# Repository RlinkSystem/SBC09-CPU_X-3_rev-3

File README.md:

# SBC09-CPU_X-3_rev-3

Simple SBC design around MC6809 Revision 3

This is the second atemp/test to make a full SBC system based on my old
modem X-3 construction, and keep it simpel.

This was done during Summer holiday 2025.
To test my simple & basic setup, and continue to experiment.

My goal is to have an uncomplex build that is not compact, so:
* not with a few large ICs
* not with PAL/GAL
* and with "many" ICs

So my setup is:
* CPU: MC68B09/HD63C09
* MEM: 7x HM6264ALP-15
* ROM: 2764 eq EPROM / EEPROM
* PTM: MC6840
* ACIA: 2x MC6850
* ACIA: R6551
* PIA: 3x MC6821
* Glue logic:
  * 74HCT04
  * 4x 74HCT138
  * 74HCT4040 Baud Rate
* Test support for USB-TTL-UART
  * CH340E (CH340X)

My testing setup:

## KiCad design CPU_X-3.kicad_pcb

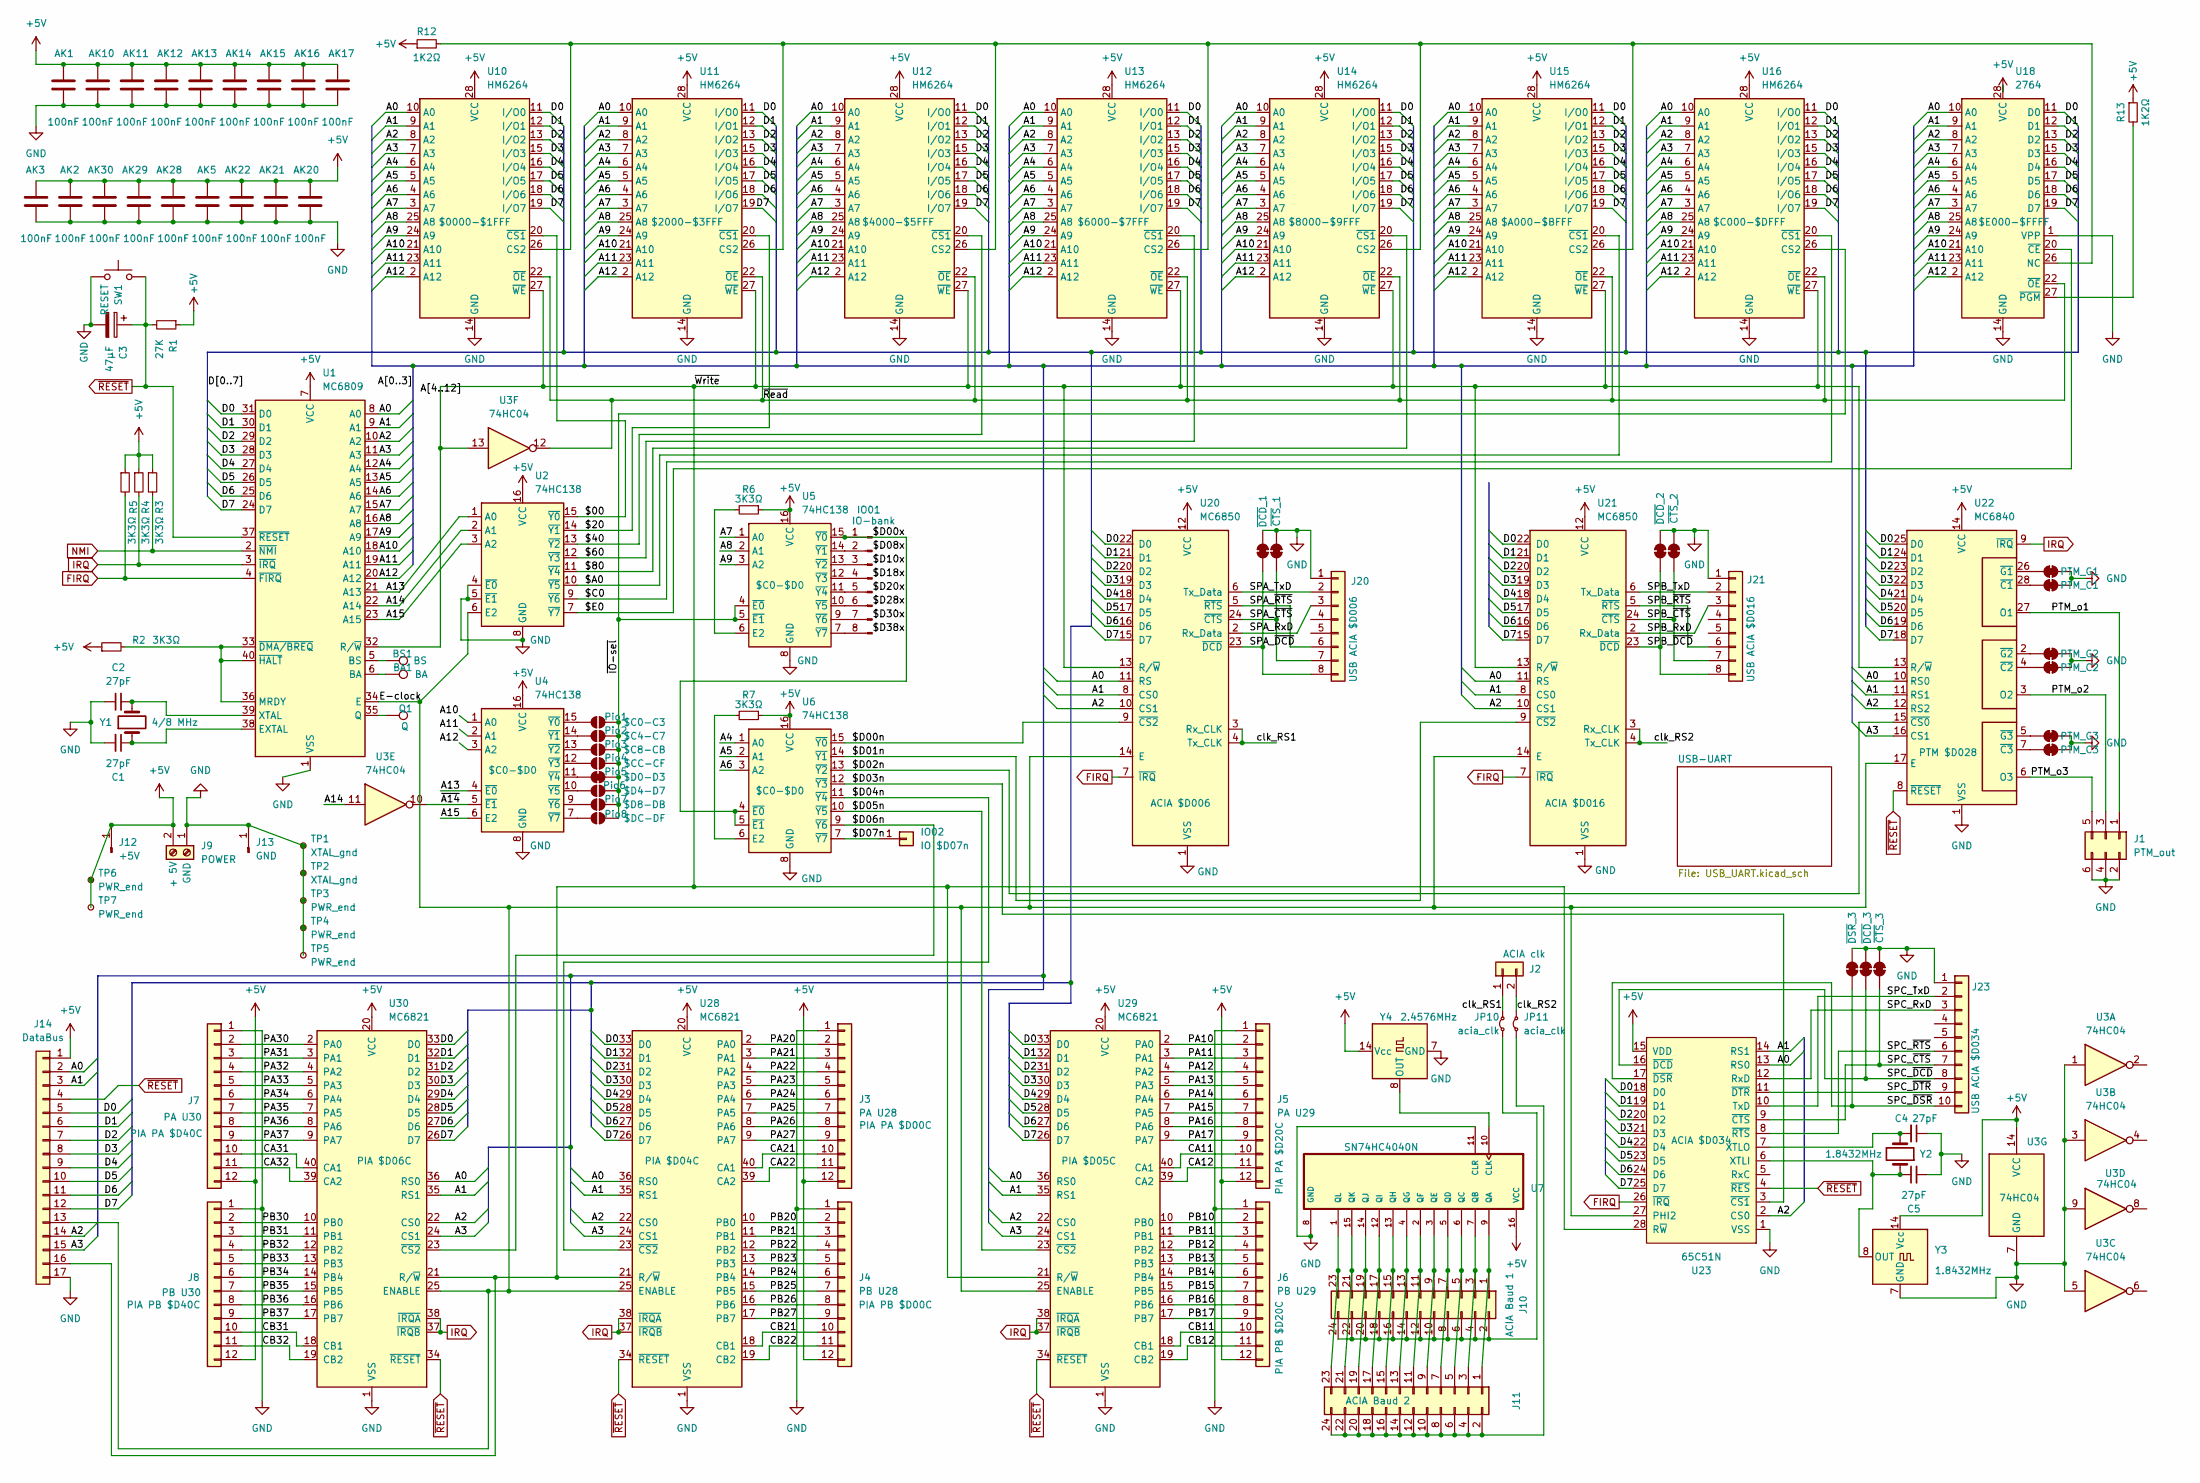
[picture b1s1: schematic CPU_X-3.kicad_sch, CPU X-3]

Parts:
AK1, AK2, AK3, AK5, AK28, AK29, AK30: 100nF; Avkopplings_C
AK10, AK11, AK12, AK13, AK14, AK15, AK16, AK17, AK20, AK21, AK22: 100nF; Avkoppling_LC
BA1: BA; TestPoint_Pad_1.5x1.5mm
BS1: BS; TestPoint_Pad_1.5x1.5mm
C1, C2, C4, C5: 27pF; C_Rect_L4.0mm_W2.5mm_P2.50mm
C3: 47µF; CP_Axial_L11.0mm_D6.0mm_P18.00mm_Horizontal
IO01: IO-bank; PinSocket_1x08_P2.54mm_Vertical
IO02: IO $D07n; PinSocket_1x01_P2.54mm_Vertical
J1: PTM_out; PinHeader_2x03_P2.54mm_Vertical
J2: ACIA clk; PinHeader_1x02_P2.54mm_Vertical
J3: PA U28; PinHeader_1x12_P2.54mm_Vertical
J4: PB U28; PinHeader_1x12_P2.54mm_Vertical
J5: PA U29; PinHeader_1x12_P2.54mm_Vertical
J6: PB U29; PinHeader_1x12_P2.54mm_Vertical
J7: PA U30; PinHeader_1x12_P2.54mm_Vertical
J8: PB U30; PinHeader_1x12_P2.54mm_Vertical
J9: POWER; TerminalBlock_MetzConnect_Type101_RT01602HBWC_1x02_P5.08mm_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
J10: ACIA Baud 1; PinHeader_2x12_P2.54mm_Vertical
J11: ACIA Baud 2; PinHeader_2x12_P2.54mm_Vertical
J12: +5V; Pin_D1.0mm_L10.0mm_LooseFit
J13: GND; Pin_D1.0mm_L10.0mm_LooseFit
J14: DataBus; PinHeader_1x17_P2.54mm_Vertical
J20: USB ACIA $D006; PinSocket_1x08_P2.54mm_Vertical
J21: USB ACIA $D016; PinSocket_1x08_P2.54mm_Vertical
J23: USB ACIA $D034; PinSocket_1x10_P2.54mm_Vertical
JP10, JP11: acia_clk; SolderJumper-2_P1.3mm_Bridged_RoundedPad1.0x1.5mm
PTM_C1, PTM_C2, PTM_C3: PTM_1; SolderJumper-2_P1.3mm_Bridged_Pad1.0x1.5mm
PTM_G1, PTM_G2, PTM_G3: PTM_1; SolderJumper-2_P1.3mm_Bridged_Pad1.0x1.5mm
Pio1: $C0-C3; SolderJumper-2_P1.3mm_Open_RoundedPad1.0x1.5mm
Pio2: $C4-C7; SolderJumper-2_P1.3mm_Open_RoundedPad1.0x1.5mm
Pio3: $C8-CB; SolderJumper-2_P1.3mm_Open_RoundedPad1.0x1.5mm
Pio4: $CC-CF; SolderJumper-2_P1.3mm_Open_RoundedPad1.0x1.5mm
Pio5: $D0-D3; SolderJumper-2_P1.3mm_Bridged_RoundedPad1.0x1.5mm
Pio6: $D4-D7; SolderJumper-2_P1.3mm_Open_RoundedPad1.0x1.5mm
Pio7: $D8-DB; SolderJumper-2_P1.3mm_Open_RoundedPad1.0x1.5mm
Pio8: $DC-DF; SolderJumper-2_P1.3mm_Open_RoundedPad1.0x1.5mm
Q1: Q; TestPoint_Pad_1.5x1.5mm
R1: 27K; R_Axial_DIN0207_L6.3mm_D2.5mm_P10.16mm_Horizontal
R2, R3, R4, R5, R6, R7: 3K3Ω; R_Axial_DIN0207_L6.3mm_D2.5mm_P10.16mm_Horizontal
R12: 1K2Ω; R_Axial_PullUp_long
R13: 1K2Ω; R_Axial_DIN0207_L6.3mm_D2.5mm_P10.16mm_Horizontal
SW1: RESET; SW_PUSH_1P1T_6x3.5mm_H5.0_APEM_MJTP1250
TP1, TP2: XTAL_gnd; TestPoint_Pad_D1.0mm
TP3, TP4, TP5, TP6, TP7: PWR_end; TestPoint_Pad_D1.0mm
U1: MC6809; DIP-40_W15.24mm_Socket_LongPads
U2, U4, U5, U6: 74HC138; DIP-16_W7.62mm_Socket_LongPads
U3: 74HC04; DIP-14_W7.62mm_Socket_LongPads
U7: SN74HC4040N; DIP-16_W7.62mm_Socket_LongPads
U10, U11, U12, U13, U14, U16: HM6264; X3-MEM_DIP-28
U15: HM6264; DIP_Socket-28_W11.9_W12.7_W15.24_W17.78_W18.5_3M_228-1277-0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
U18: 2764; X3-MEM_DIP-28
U20, U21: MC6850; DIP-24_18.0mmx34.29mm_W15.24mm_Socket_LongPads
U22: MC6840; DIP-28_W15.24mm_Socket_LongPads
U23: 65C51N; DIP-28_W15.24mm
U28, U29, U30: MC6821; X3-IO_DIP-40
Y1: 4/8 MHz; Resonator-2Pin_W10.0mm_H5.0mm
Y2: 1.8432MHz; Resonator-2Pin_W10.0mm_H5.0mm
Y3: 1.8432MHz; Oscillator_DIP-14
Y4: 2.4576MHz; Oscillator_DIP-14
~{CTS}_1: UART-A; SolderJumper-2_P1.3mm_Bridged_Pad1.0x1.5mm
~{CTS}_2: UART-B; SolderJumper-2_P1.3mm_Bridged_Pad1.0x1.5mm
~{CTS}_3: UART-C; SolderJumper-2_P1.3mm_Bridged_Pad1.0x1.5mm
~{DCD}_1: UART-A; SolderJumper-2_P1.3mm_Bridged_Pad1.0x1.5mm
~{DCD}_2: UART-B; SolderJumper-2_P1.3mm_Bridged_Pad1.0x1.5mm
~{DCD}_3: UART-C; SolderJumper-2_P1.3mm_Bridged_Pad1.0x1.5mm
~{DSR}_3: UART-C; SolderJumper-2_P1.3mm_Bridged_Pad1.0x1.5mm

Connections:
+5V: AK1.1, AK2.1, AK3.1, AK5.1, AK10.1, AK11.1, AK12.1, AK13.1, AK14.1, AK15.1, AK16.1, AK17.1, AK20.1, AK21.1, AK22.1, AK28.1, AK29.1, AK30.1, J3.12, J4.12, J5.12, J6.12, J7.12, J8.12, J9.2, J12.1, J14.1, R1.1, R2.1, R3.1, R4.1, R5.1, R6.1, R7.1, R12.1, R13.1, TP6.1, TP7.1, U1.7 (VCC), U2.16 (VCC), U3.14 (VCC), U4.16 (VCC), U5.16 (VCC), U6.16 (VCC), U7.16 (VCC), U10.28 (VCC), U11.28 (VCC), U12.28 (VCC), U13.28 (VCC), U14.28 (VCC), U15.28 (VCC), U16.28 (VCC), U18.28 (VCC), U20.12 (VCC), U21.12 (VCC), U22.14 (VCC), U23.15 (VDD), U28.20 (VCC), U29.20 (VCC), U30.20 (VCC), Y3.14 (Vcc), Y4.14 (Vcc); also elsewhere on the board
/$00: U2.15 (~Y0), U10.20 (~CS1)
/$20: U2.14 (~Y1), U11.20 (~CS1)
/$40: U2.13 (~Y2), U12.20 (~CS1)
/$60: U2.12 (~Y3), U13.20 (~CS1)
/$80: U2.11 (~Y4), U14.20 (~CS1)
/$A0: U2.10 (~Y5), U15.20 (~CS1)
/$C0: U2.9 (~Y6), U16.20 (~CS1)
/$D00n: U6.15 (~Y0), U20.9 (~CS2)
/$D00x: IO01.1, U5.15 (~Y0), U6.4 (~E0), U6.5 (~E1)
/$D01n: U6.14 (~Y1), U21.9 (~CS2)
/$D02n: U6.13 (~Y2), U22.15 (~CS0)
/$D03n: U6.12 (~Y3), U23.3 (~CS1)
/$D04n: U6.11 (~Y4), U28.23 (~CS2)
/$D05n: U6.10 (~Y5), U29.23 (~CS2)
/$D06n: U6.9 (~Y6), U30.23 (~CS2)
/$D07n: IO02.1, U6.7 (~Y7)
/$E0: U2.7 (~Y7), U18.20 (~CE)
/A0: J14.2, U1.8 (A0), U10.10 (A0), U11.10 (A0), U12.10 (A0), U13.10 (A0), U14.10 (A0), U15.10 (A0), U16.10 (A0), U18.10 (A0), U20.11 (RS), U21.11 (RS), U22.10 (RS0), U23.13 (RS0), U28.36 (RS0), U29.36 (RS0), U30.36 (RS0)
/A1: J14.3, U1.9 (A1), U10.9 (A1), U11.9 (A1), U12.9 (A1), U13.9 (A1), U14.9 (A1), U15.9 (A1), U16.9 (A1), U18.9 (A1), U20.8 (CS0), U21.8 (CS0), U22.11 (RS1), U23.14 (RS1), U28.35 (RS1), U29.35 (RS1), U30.35 (RS1)
/A2: J14.14, U1.10 (A2), U10.8 (A2), U11.8 (A2), U12.8 (A2), U13.8 (A2), U14.8 (A2), U15.8 (A2), U16.8 (A2), U18.8 (A2), U20.10 (CS1), U21.10 (CS1), U22.12 (RS2), U23.2 (CS0), U28.22 (CS0), U29.22 (CS0), U30.22 (CS0)
/A3: J14.15, U1.11 (A3), U10.7 (A3), U11.7 (A3), U12.7 (A3), U13.7 (A3), U14.7 (A3), U15.7 (A3), U16.7 (A3), U18.7 (A3), U22.16 (CS1), U28.24 (CS1), U29.24 (CS1), U30.24 (CS1)
/A4: U1.12 (A4), U6.1 (A0), U10.6 (A4), U11.6 (A4), U12.6 (A4), U13.6 (A4), U14.6 (A4), U15.6 (A4), U16.6 (A4), U18.6 (A4)
/A5: U1.13 (A5), U6.2 (A1), U10.5 (A5), U11.5 (A5), U12.5 (A5), U13.5 (A5), U14.5 (A5), U15.5 (A5), U16.5 (A5), U18.5 (A5)
/A6: U1.14 (A6), U6.3 (A2), U10.4 (A6), U11.4 (A6), U12.4 (A6), U13.4 (A6), U14.4 (A6), U15.4 (A6), U16.4 (A6), U18.4 (A6)
/A7: U1.15 (A7), U5.1 (A0), U10.3 (A7), U11.3 (A7), U12.3 (A7), U13.3 (A7), U14.3 (A7), U15.3 (A7), U16.3 (A7), U18.3 (A7)
/A8: U1.16 (A8), U5.2 (A1), U10.25 (A8), U11.25 (A8), U12.25 (A8), U13.25 (A8), U14.25 (A8), U15.25 (A8), U16.25 (A8), U18.25 (A8)
/A9: U1.17 (A9), U5.3 (A2), U10.24 (A9), U11.24 (A9), U12.24 (A9), U13.24 (A9), U14.24 (A9), U15.24 (A9), U16.24 (A9), U18.24 (A9)
/A10: U1.18 (A10), U4.1 (A0), U10.21 (A10), U11.21 (A10), U12.21 (A10), U13.21 (A10), U14.21 (A10), U15.21 (A10), U16.21 (A10), U18.21 (A10)
/A11: U1.19 (A11), U4.2 (A1), U10.23 (A11), U11.23 (A11), U12.23 (A11), U13.23 (A11), U14.23 (A11), U15.23 (A11), U16.23 (A11), U18.23 (A11)
/A12: U1.20 (A12), U4.3 (A2), U10.2 (A12), U11.2 (A12), U12.2 (A12), U13.2 (A12), U14.2 (A12), U15.2 (A12), U16.2 (A12), U18.2 (A12)
/A13: U1.21 (A13), U2.1 (A0), U4.4 (~E0)
/A14: U1.22 (A14), U2.2 (A1), U3.11
/A15: U1.23 (A15), U2.3 (A2), U4.6 (E2)
/CA11: J5.10, U29.40 (CA1)
/CA12: J5.11, U29.39 (CA2)
/CA21: J3.10, U28.40 (CA1)
/CA22: J3.11, U28.39 (CA2)
/CA31: J7.10, U30.40 (CA1)
/CA32: J7.11, U30.39 (CA2)
/CB11: J6.10, U29.18 (CB1)
/CB12: J6.11, U29.19 (CB2)
/CB21: J4.10, U28.18 (CB1)
/CB22: J4.11, U28.19 (CB2)
/CB31: J8.10, U30.18 (CB1)
/CB32: J8.11, U30.19 (CB2)
/D0: J14.5, U1.31 (D0), U10.11 (I/O0), U11.11 (I/O0), U12.11 (I/O0), U13.11 (I/O0), U14.11 (I/O0), U15.11 (I/O0), U16.11 (I/O0), U18.11 (D0), U20.22 (D0), U21.22 (D0), U22.25 (D0), U23.18 (D0), U28.33 (D0), U29.33 (D0), U30.33 (D0)
/D1: J14.6, U1.30 (D1), U10.12 (I/O1), U11.12 (I/O1), U12.12 (I/O1), U13.12 (I/O1), U14.12 (I/O1), U15.12 (I/O1), U16.12 (I/O1), U18.12 (D1), U20.21 (D1), U21.21 (D1), U22.24 (D1), U23.19 (D1), U28.32 (D1), U29.32 (D1), U30.32 (D1)
/D2: J14.7, U1.29 (D2), U10.13 (I/O2), U11.13 (I/O2), U12.13 (I/O2), U13.13 (I/O2), U14.13 (I/O2), U15.13 (I/O2), U16.13 (I/O2), U18.13 (D2), U20.20 (D2), U21.20 (D2), U22.23 (D2), U23.20 (D2), U28.31 (D2), U29.31 (D2), U30.31 (D2)
/D3: J14.8, U1.28 (D3), U10.15 (I/O3), U11.15 (I/O3), U12.15 (I/O3), U13.15 (I/O3), U14.15 (I/O3), U15.15 (I/O3), U16.15 (I/O3), U18.15 (D3), U20.19 (D3), U21.19 (D3), U22.22 (D3), U23.21 (D3), U28.30 (D3), U29.30 (D3), U30.30 (D3)
/D4: J14.9, U1.27 (D4), U10.16 (I/O4), U11.16 (I/O4), U12.16 (I/O4), U13.16 (I/O4), U14.16 (I/O4), U15.16 (I/O4), U16.16 (I/O4), U18.16 (D4), U20.18 (D4), U21.18 (D4), U22.21 (D4), U23.22 (D4), U28.29 (D4), U29.29 (D4), U30.29 (D4)
/D5: J14.10, U1.26 (D5), U10.17 (I/O5), U11.17 (I/O5), U12.17 (I/O5), U13.17 (I/O5), U14.17 (I/O5), U15.17 (I/O5), U16.17 (I/O5), U18.17 (D5), U20.17 (D5), U21.17 (D5), U22.20 (D5), U23.23 (D5), U28.28 (D5), U29.28 (D5), U30.28 (D5)
/D6: J14.11, U1.25 (D6), U10.18 (I/O6), U11.18 (I/O6), U12.18 (I/O6), U13.18 (I/O6), U14.18 (I/O6), U15.18 (I/O6), U16.18 (I/O6), U18.18 (D6), U20.16 (D6), U21.16 (D6), U22.19 (D6), U23.24 (D6), U28.27 (D6), U29.27 (D6), U30.27 (D6)
/D7: J14.12, U1.24 (D7), U10.19 (I/O7), U11.19 (I/O7), U12.19 (I/O7), U13.19 (I/O7), U14.19 (I/O7), U15.19 (I/O7), U16.19 (I/O7), U18.19 (D7), U20.15 (D7), U21.15 (D7), U22.18 (D7), U23.25 (D7), U28.26 (D7), U29.26 (D7), U30.26 (D7)
/E-clock: J14.13, U1.34 (E), U2.6 (E2), U20.14 (E), U21.14 (E), U22.17 (E), U23.27 (PHI2), U28.25 (ENABLE), U29.25 (ENABLE), U30.25 (ENABLE)
/PA10: J5.2, U29.2 (PA0)
/PA11: J5.3, U29.3 (PA1)
/PA12: J5.4, U29.4 (PA2)
/PA13: J5.5, U29.5 (PA3)
/PA14: J5.6, U29.6 (PA4)
/PA15: J5.7, U29.7 (PA5)
/PA16: J5.8, U29.8 (PA6)
/PA17: J5.9, U29.9 (PA7)
/PA20: J3.2, U28.2 (PA0)
/PA21: J3.3, U28.3 (PA1)
/PA22: J3.4, U28.4 (PA2)
/PA23: J3.5, U28.5 (PA3)
/PA24: J3.6, U28.6 (PA4)
/PA25: J3.7, U28.7 (PA5)
/PA26: J3.8, U28.8 (PA6)
/PA27: J3.9, U28.9 (PA7)
/PA30: J7.2, U30.2 (PA0)
/PA31: J7.3, U30.3 (PA1)
/PA32: J7.4, U30.4 (PA2)
/PA33: J7.5, U30.5 (PA3)
/PA34: J7.6, U30.6 (PA4)
/PA35: J7.7, U30.7 (PA5)
/PA36: J7.8, U30.8 (PA6)
/PA37: J7.9, U30.9 (PA7)
/PB10: J6.2, U29.10 (PB0)
/PB11: J6.3, U29.11 (PB1)
/PB12: J6.4, U29.12 (PB2)
/PB13: J6.5, U29.13 (PB3)
/PB14: J6.6, U29.14 (PB4)
/PB15: J6.7, U29.15 (PB5)
/PB16: J6.8, U29.16 (PB6)
/PB17: J6.9, U29.17 (PB7)
/PB20: J4.2, U28.10 (PB0)
/PB21: J4.3, U28.11 (PB1)
/PB22: J4.4, U28.12 (PB2)
/PB23: J4.5, U28.13 (PB3)
/PB24: J4.6, U28.14 (PB4)
/PB25: J4.7, U28.15 (PB5)
/PB26: J4.8, U28.16 (PB6)
/PB27: J4.9, U28.17 (PB7)
/PB30: J8.2, U30.10 (PB0)
/PB31: J8.3, U30.11 (PB1)
/PB32: J8.4, U30.12 (PB2)
/PB33: J8.5, U30.13 (PB3)
/PB34: J8.6, U30.14 (PB4)
/PB35: J8.7, U30.15 (PB5)
/PB36: J8.8, U30.16 (PB6)
/PB37: J8.9, U30.17 (PB7)
/PTM_o1: J1.1, U22.27 (O1)
/PTM_o2: J1.3, U22.3 (O2)
/PTM_o3: J1.5, U22.6 (O3)
/SPA_TxD: J20.2, U20.6 (Tx_Data)
/SPA_~CTS: J20.7, U20.24 (~CTS), ~{CTS}_1.1 (A)
/SPA_~DCD: J20.8, U20.23 (~DCD), ~{DCD}_1.1 (A)
/SPA_~RTS: J20.6, U20.5 (~RTS)
/SPB_RxD: J21.3, U21.2 (Rx_Data)
/SPB_TxD: J21.2, U21.6 (Tx_Data)
/SPB_~CTS: J21.7, U21.24 (~CTS), ~{CTS}_2.1 (A)
/SPB_~DCD: J21.8, U21.23 (~DCD), ~{DCD}_2.1 (A)
/SPB_~RTS: J21.6, U21.5 (~RTS)
/SPC_RxD: J23.3, U23.12 (RxD)
/SPC_TxD: J23.2, U23.10 (TxD)
/SPC_~CTS: J23.7, U23.9 (~CTS), ~{CTS}_3.1 (A)
/SPC_~DCD: J23.8, U23.16 (~DCD), ~{DCD}_3.1 (A)
/SPC_~DSR: J23.10, U23.17 (~DSR), ~{DSR}_3.1 (A)
/SPC_~DTR: J23.9, U23.11 (~DTR)
/SPC_~RTS: J23.6, U23.8 (~RTS)
/clk_RS1: J2.1, JP10.2 (B), U20.3 (Rx_CLK), U20.4 (Tx_CLK)
/clk_RS2: J2.2, JP11.2 (B), U21.3 (Rx_CLK), U21.4 (Tx_CLK)
/~A14: U3.10, U4.5 (~E1)
/~IO-sel: Pio1.2 (B), Pio2.2 (B), Pio3.2 (B), Pio4.2 (B), Pio5.2 (B), Pio6.2 (B), Pio7.2 (B), Pio8.2 (B), U5.4 (~E0), U5.5 (~E1), U16.26 (CS2)
/~Read: U3.12, U10.22 (~OE), U11.22 (~OE), U12.22 (~OE), U13.22 (~OE), U14.22 (~OE), U15.22 (~OE), U16.22 (~OE), U18.22 (~OE)
/~Write: J14.16, U1.32 (R/~W), U3.13, U10.27 (~WE), U11.27 (~WE), U12.27 (~WE), U13.27 (~WE), U14.27 (~WE), U15.27 (~WE), U16.27 (~WE), U20.13 (R/~W), U21.13 (R/~W), U22.13 (R/~W), U23.28 (R~W), U28.21 (R/~W), U29.21 (R/~W), U30.21 (R/~W)
FIRQ: R5.2, U1.4 (~FIRQ), U20.7 (~IRQ), U21.7 (~IRQ), U23.26 (~IRQ)
GND: AK1.2, AK2.2, AK3.2, AK5.2, AK10.2, AK11.2, AK12.2, AK13.2, AK14.2, AK15.2, AK16.2, AK17.2, AK20.2, AK21.2, AK22.2, AK28.2, AK29.2, AK30.2, C1.2, C2.1, C3.2, C4.1, C5.2, J1.2, J1.4, J1.6, J3.1, J4.1, J5.1, J6.1, J7.1, J8.1, J9.1, J13.1, J14.17, J20.1, J21.1, J23.1, PTM_C1.2 (B), PTM_C2.2 (B), PTM_C3.2 (B), PTM_G1.2 (B), PTM_G2.2 (B), PTM_G3.2 (B), SW1.1, TP1.1, TP2.1, TP3.1, TP4.1, TP5.1, U1.1 (VSS), U2.4 (~E0), U2.5 (~E1), U2.8 (GND), U3.1, U3.3, U3.5, U3.7 (GND), U3.9, U4.8 (GND), U5.8 (GND), U6.8 (GND), U7.8 (GND), U7.11 (CLR), U10.14 (GND), U11.14 (GND), U12.14 (GND), U13.14 (GND), U14.14 (GND), U15.14 (GND), U16.14 (GND), U18.1 (VPP), U18.14 (GND), U20.1 (VSS), U21.1 (VSS), U22.1 (VSS), U23.1 (VSS), U28.1 (VSS), U29.1 (VSS), U30.1 (VSS), Y3.7 (GND), Y4.7 (GND), ~{CTS}_1.2 (B), ~{CTS}_2.2 (B), ~{CTS}_3.2 (B), ~{DCD}_1.2 (B), ~{DCD}_2.2 (B), ~{DCD}_3.2 (B), ~{DSR}_3.2 (B); also elsewhere on the board
IRQ: R4.2, U1.3 (~IRQ), U22.9 (~IRQ), U28.37 (~IRQB), U28.38 (~IRQA), U29.37 (~IRQB), U29.38 (~IRQA), U30.37 (~IRQB), U30.38 (~IRQA)
NMI: R3.2, U1.2 (~NMI)
unnamed: IO01.2, U5.14 (~Y1)
unnamed: IO01.3, U5.13 (~Y2)
unnamed: IO01.4, U5.12 (~Y3)
unnamed: IO01.5, U5.11 (~Y4)
unnamed: IO01.6, U5.10 (~Y5)
unnamed: IO01.7, U5.9 (~Y6)
unnamed: IO01.8, U5.7 (~Y7)
unnamed: J10.1, J11.1, U7.9 (QA)
unnamed: J10.3, J11.3, U7.7 (QB)
unnamed: J10.5, J11.5, U7.6 (QC)
unnamed: J10.7, J11.7, U7.5 (QD)
unnamed: J10.9, J11.9, U7.3 (QE)
unnamed: J10.2, J10.4, J10.6, J10.8, J10.10, J10.12, J10.14, J10.16, J10.18, J10.20, J10.22, J10.24, JP10.1 (A)
unnamed: J10.11, J11.11, U7.2 (QF)
unnamed: J10.13, J11.13, U7.4 (QG)
unnamed: J10.15, J11.15, U7.13 (QH)
unnamed: J10.17, J11.17, U7.12 (QI)
unnamed: J10.19, J11.19, U7.14 (QJ)
unnamed: J10.21, J11.21, U7.15 (QK)
unnamed: J10.23, J11.23, U7.1 (QL)
unnamed: J11.2, J11.4, J11.6, J11.8, J11.10, J11.12, J11.14, J11.16, J11.18, J11.20, J11.22, J11.24, JP11.1 (A)
unnamed: J20.3, U20.2 (Rx_Data)
unnamed: PTM_C1.1 (A), U22.28 (~C1)
unnamed: PTM_C2.1 (A), U22.4 (~C2)
unnamed: PTM_C3.1 (A), U22.7 (~C3)
unnamed: PTM_G1.1 (A), U22.26 (~G1)
unnamed: PTM_G2.1 (A), U22.2 (~G2)
unnamed: PTM_G3.1 (A), U22.5 (~G3)
unnamed: Pio1.1 (A), U4.15 (~Y0)
unnamed: Pio2.1 (A), U4.14 (~Y1)
unnamed: Pio3.1 (A), U4.13 (~Y2)
unnamed: Pio4.1 (A), U4.12 (~Y3)
unnamed: Pio5.1 (A), U4.11 (~Y4)
unnamed: Pio6.1 (A), U4.10 (~Y5)
unnamed: Pio7.1 (A), U4.9 (~Y6)
unnamed: Pio8.1 (A), U4.7 (~Y7)
unnamed: BA1.1, U1.6 (BA)
unnamed: BS1.1, U1.5 (BS)
unnamed: C1.1, U1.38 (EXTAL), Y1.1
unnamed: R2.2, U1.33 (~DMA/BREQ), U1.36 (MRDY), U1.40 (~HALT)
unnamed: Q1.1, U1.35 (Q)
unnamed: C2.2, U1.39 (XTAL), Y1.2
unnamed: R6.2, U5.6 (E2)
unnamed: R7.2, U6.6 (E2)
unnamed: U7.10 (CLK), Y4.8 (OUT)
unnamed: R12.2, U10.26 (CS2), U11.26 (CS2), U12.26 (CS2), U13.26 (CS2), U14.26 (CS2), U15.26 (CS2), U18.26 (NC)
unnamed: R13.2, U18.27 (~PGM)
unnamed: C5.1, U23.6 (XTLI), Y2.1, Y3.8 (OUT)
unnamed: C4.2, U23.7 (XTLO), Y2.2
~RESET: C3.1, J14.4, R1.2, SW1.2, U1.37 (~RESET), U22.8 (~RESET), U23.4 (~RES), U28.34 (~RESET), U29.34 (~RESET), U30.34 (~RESET)

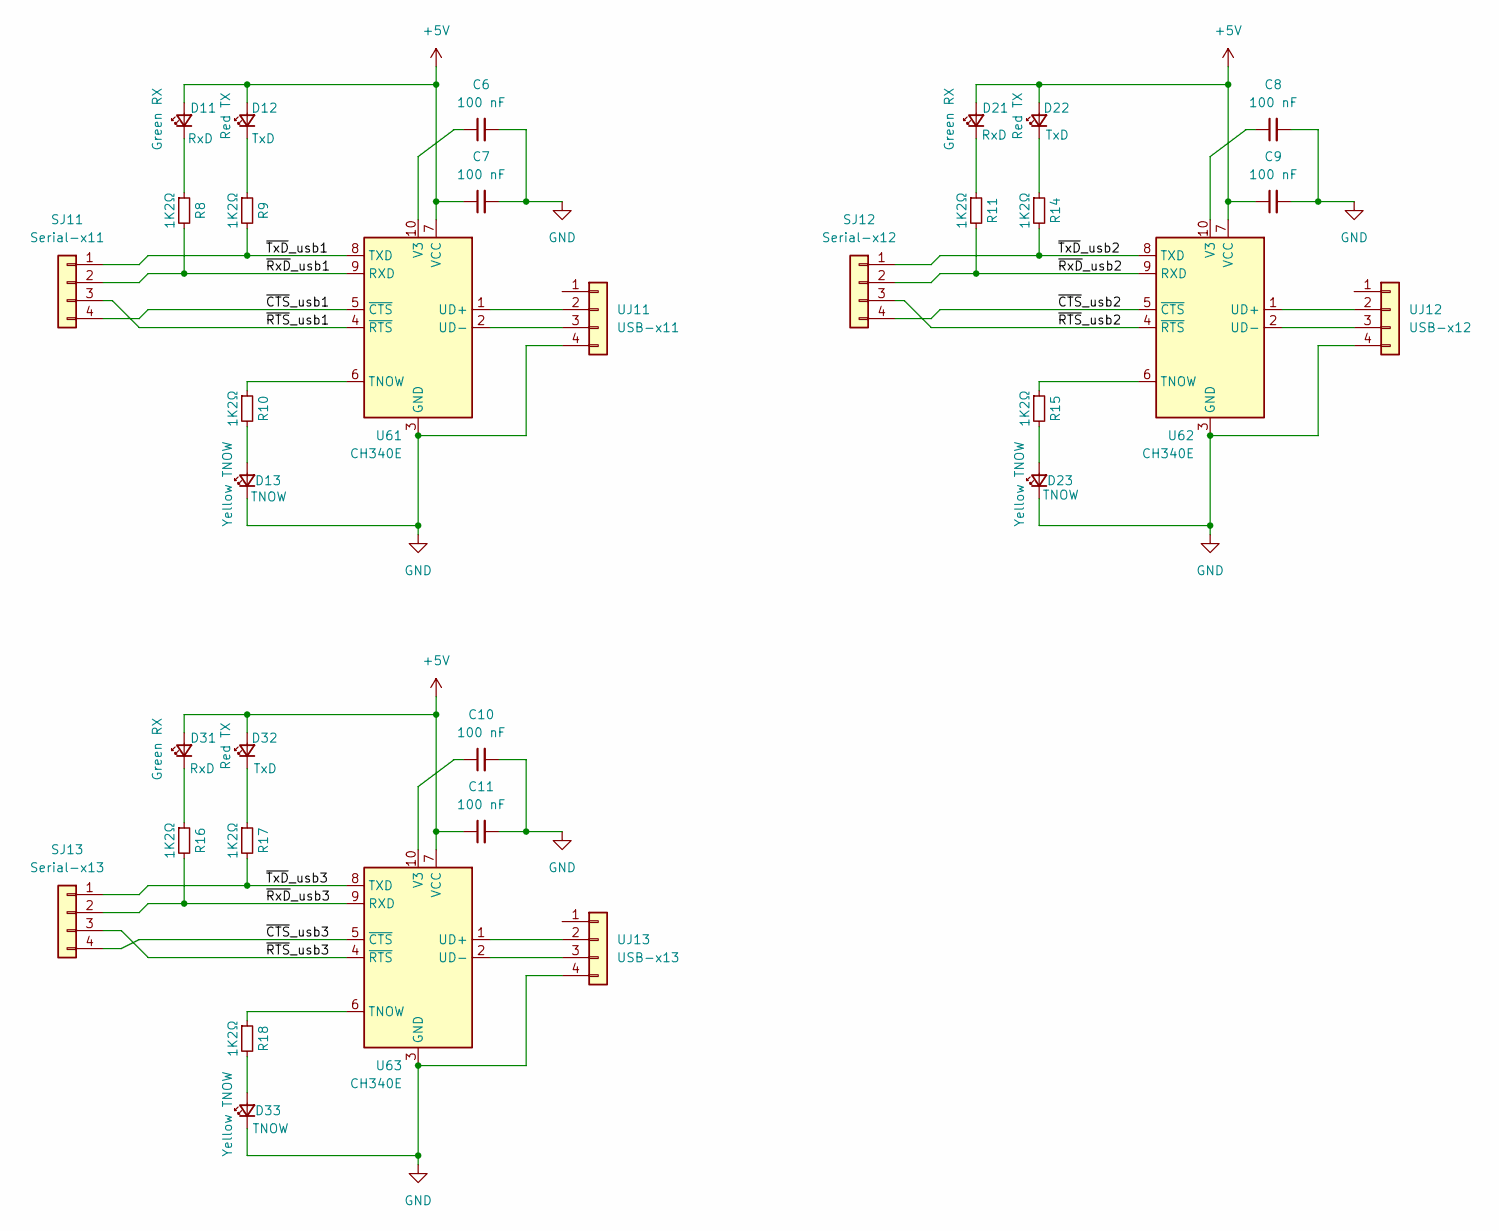
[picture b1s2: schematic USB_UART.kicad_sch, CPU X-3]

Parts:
C6, C7, C8, C9, C10, C11: 100 nF; C_Axial_L3.8mm_D2.6mm_P7.50mm_Horizontal
D11, D21, D31: Green RX; LED_D3.0mm
D12, D22, D32: Red TX; LED_D3.0mm
D13, D23, D33: Yellow TNOW; LED_D3.0mm
R8, R9, R10, R11, R14, R15, R16, R17, R18: 1K2Ω; R_Axial_DIN0207_L6.3mm_D2.5mm_P10.16mm_Horizontal
SJ11: Serial-x11; PinHeader_1x04_P2.54mm_Vertical
SJ12: Serial-x12; PinHeader_1x04_P2.54mm_Vertical
SJ13: Serial-x13; PinHeader_1x04_P2.54mm_Vertical
U61, U62, U63: CH340E; MSOP-10_3x3mm_P0.5mm-CH340E
UJ11: USB-x11; PinHeader_1x04_P2.54mm_Vertical
UJ12: USB-x12; PinHeader_1x04_P2.54mm_Vertical
UJ13: USB-x13; PinHeader_1x04_P2.54mm_Vertical

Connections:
+5V: C7.1, C9.1, C11.1, D11.2 (A), D12.2 (A), D21.2 (A), D22.2 (A), D31.2 (A), D32.2 (A), U61.7 (VCC), U62.7 (VCC), U63.7 (VCC); also elsewhere on the board
/USB-UART/~CTS_usb1: SJ11.4, U61.5 (~CTS)
/USB-UART/~CTS_usb2: SJ12.4, U62.5 (~CTS)
/USB-UART/~CTS_usb3: SJ13.4, U63.5 (~CTS)
/USB-UART/~RTS_usb1: SJ11.3, U61.4 (~RTS)
/USB-UART/~RTS_usb2: SJ12.3, U62.4 (~RTS)
/USB-UART/~RTS_usb3: SJ13.3, U63.4 (~RTS)
/USB-UART/~RxD_usb1: R8.2, SJ11.2, U61.9 (RXD)
/USB-UART/~RxD_usb2: R11.2, SJ12.2, U62.9 (RXD)
/USB-UART/~RxD_usb3: R16.2, SJ13.2, U63.9 (RXD)
/USB-UART/~TxD_usb1: R9.2, SJ11.1, U61.8 (TXD)
/USB-UART/~TxD_usb2: R14.2, SJ12.1, U62.8 (TXD)
/USB-UART/~TxD_usb3: R17.2, SJ13.1, U63.8 (TXD)
GND: C6.2, C7.2, C8.2, C9.2, C10.2, C11.2, D13.1 (K), D23.1 (K), D33.1 (K), U61.3 (GND), U62.3 (GND), U63.3 (GND), UJ11.4, UJ12.4, UJ13.4; also elsewhere on the board
unnamed: D11.1 (K), R8.1
unnamed: D12.1 (K), R9.1
unnamed: D13.2 (A), R10.2
unnamed: D21.1 (K), R11.1
unnamed: D22.1 (K), R14.1
unnamed: D23.2 (A), R15.2
unnamed: D31.1 (K), R16.1
unnamed: D32.1 (K), R17.1
unnamed: D33.2 (A), R18.2
unnamed: R10.1, U61.6 (TNOW)
unnamed: U61.1 (UD+), UJ11.2
unnamed: U61.2 (UD-), UJ11.3
unnamed: C6.1, U61.10 (V3)
unnamed: R15.1, U62.6 (TNOW)
unnamed: U62.1 (UD+), UJ12.2
unnamed: U62.2 (UD-), UJ12.3
unnamed: C8.1, U62.10 (V3)
unnamed: R18.1, U63.6 (TNOW)
unnamed: U63.1 (UD+), UJ13.2
unnamed: U63.2 (UD-), UJ13.3
unnamed: C10.1, U63.10 (V3)

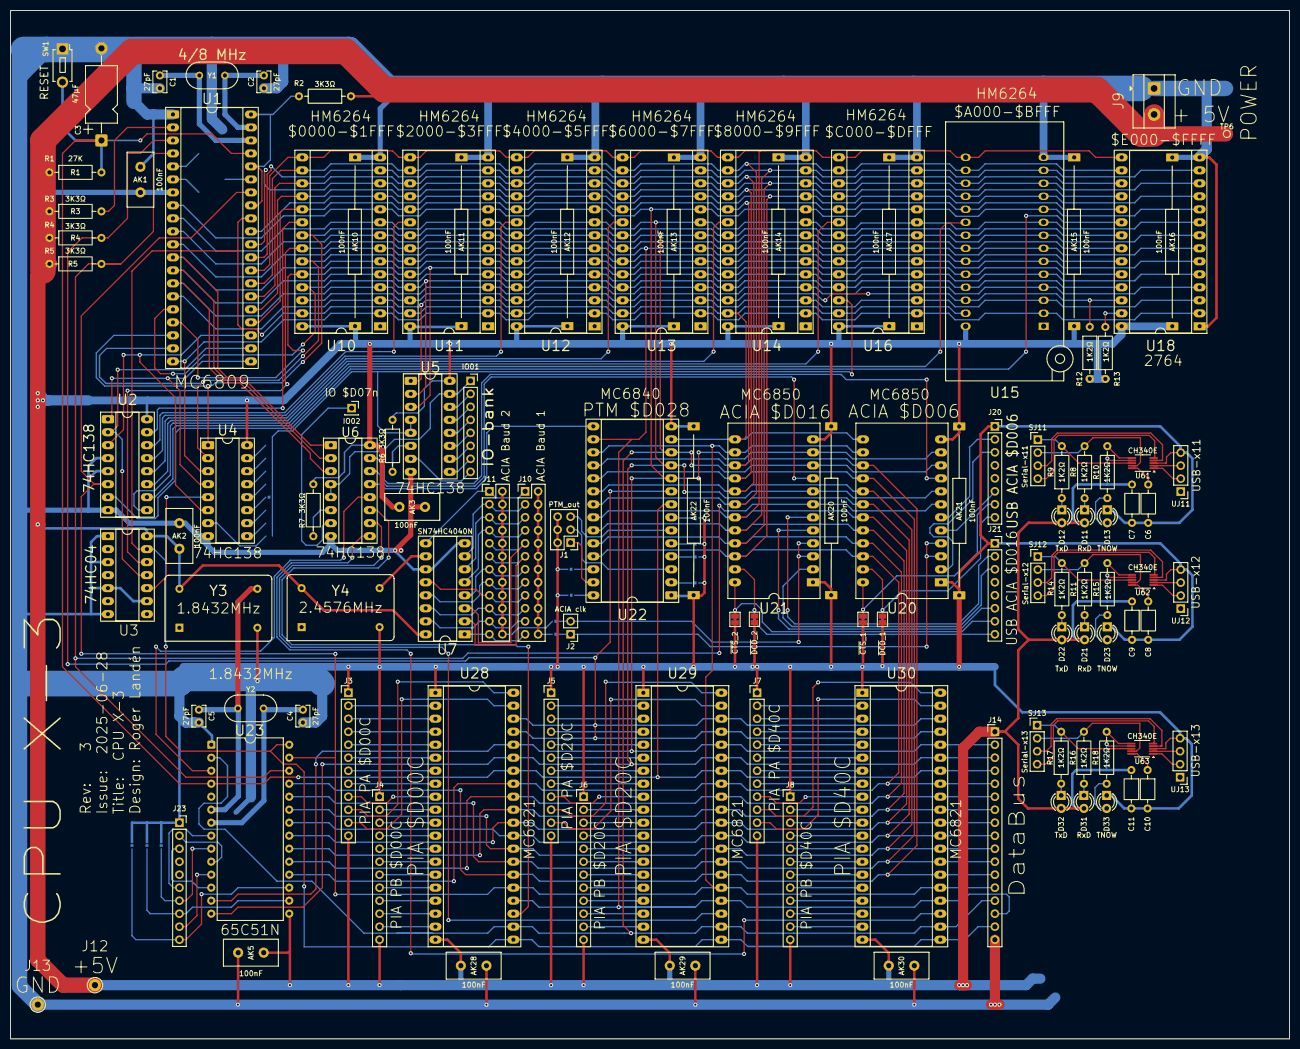
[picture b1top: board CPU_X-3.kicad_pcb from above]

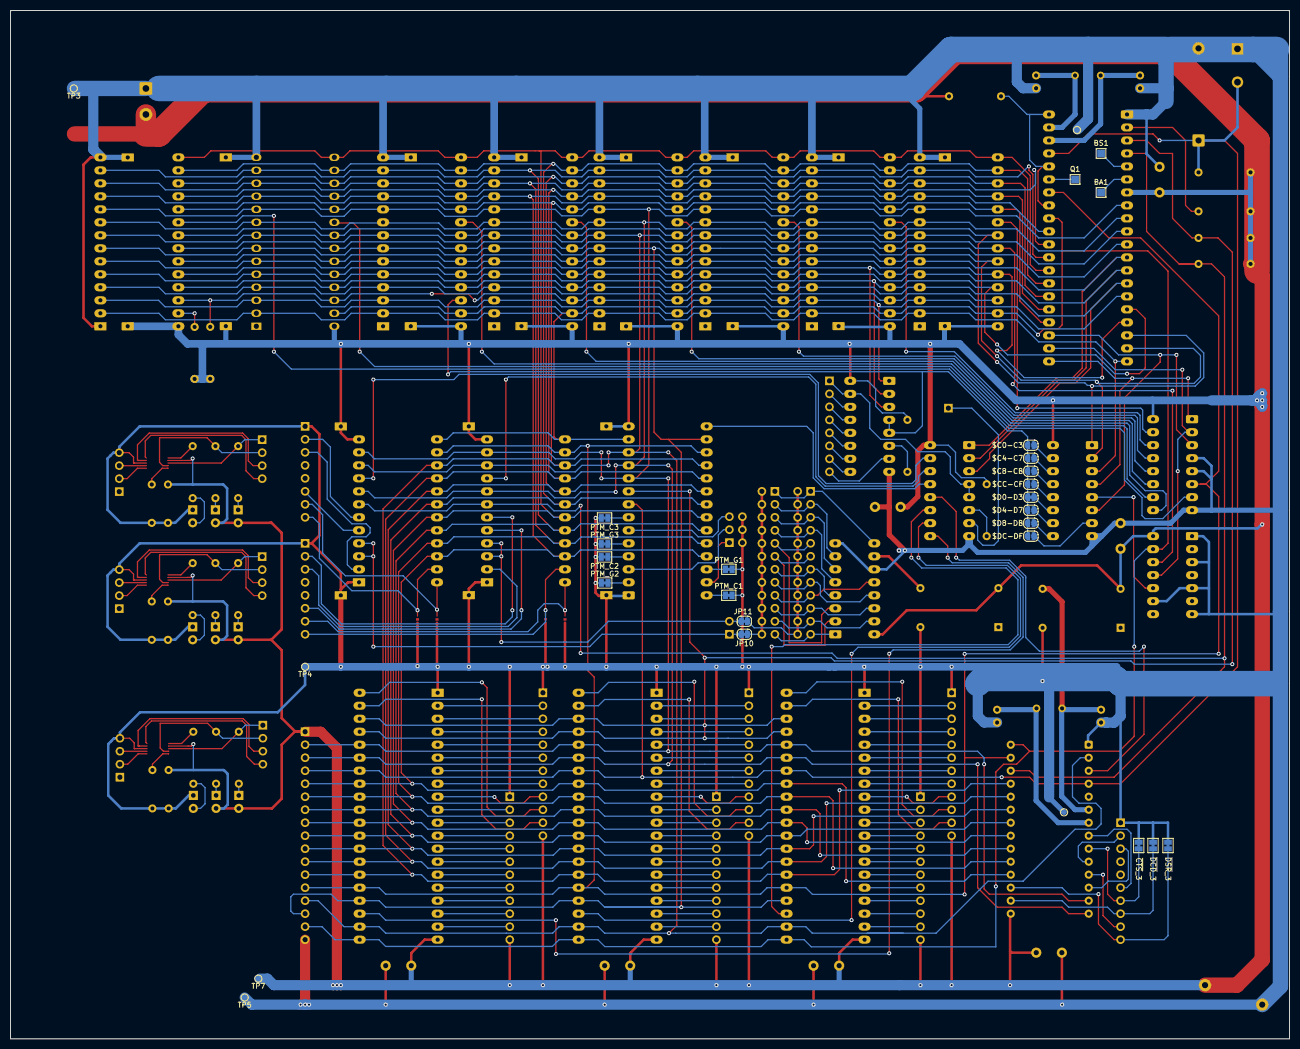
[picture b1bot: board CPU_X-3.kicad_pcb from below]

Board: 2 copper layers, 250.0 x 201.0 mm, 137 parts (25 on the bottom side), 215 nets.

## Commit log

2025-09-09 Added the KiCAD of CPU X-3 rev 3
2025-09-09 Add PCB card picture
2025-09-09 Readme picture
